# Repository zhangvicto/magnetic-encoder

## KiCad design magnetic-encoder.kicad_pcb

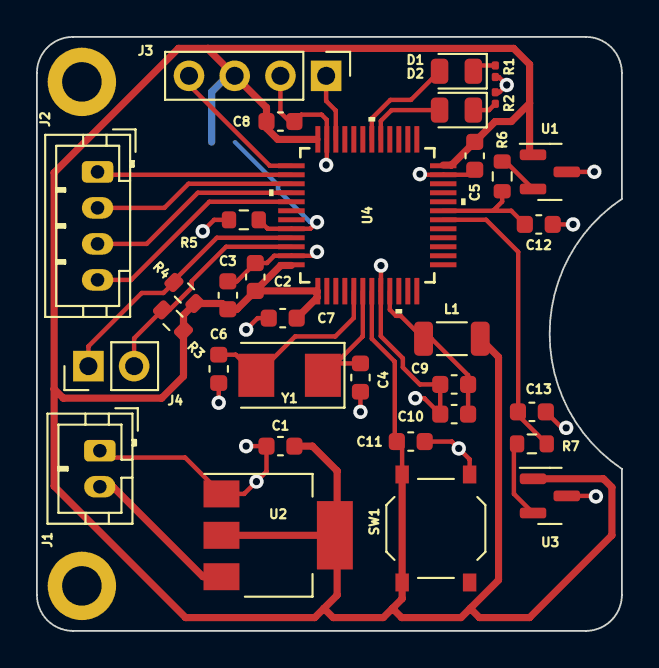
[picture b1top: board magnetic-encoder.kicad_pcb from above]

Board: 2 copper layers, 32.5 x 33.0 mm, 36 parts (1 on the bottom side), 23 nets.

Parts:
C1, C9: 1u; C_0603_1608Metric
C2: 4u7; C_0603_1608Metric
C3, C5, C7, C8, C10, C11: 100n; C_0603_1608Metric
C4, C6: 20p; L_0603_1608Metric
C12, C13: C_Small; C_0603_1608Metric
D1, D2: LED_Small; LED_0805_2012Metric
J1: Conn_01x02_Socket; JST_PH_B2B-PH-K_1x02_P2.00mm_Vertical
J2: Conn_01x04_Socket; JST_PH_B4B-PH-K_1x04_P2.00mm_Vertical
J3: Conn_01x04_Pin; PinHeader_1x04_P2.54mm_Vertical
J4: Conn_01x02_Socket; PinHeader_1x02_P2.54mm_Vertical
JP1: SolderJumper_2_Open; SolderJumper-2_P1.3mm_Open_Pad1.0x1.5mm
L1: 27n; L_1206_3216Metric
R1, R2: 1.5k; R_0201_0603Metric
R3, R4: 4.7k; R_0603_1608Metric
R5: 10k; R_0603_1608Metric
R6, R7: R_Small; R_0603_1608Metric
REF1, REF2: MountingHole_2.2mm_M2_DIN965_Pad
SW1: SW_Push; SW_Push_1P1T_XKB_TS-1187A
U1, U3: DRV5055A4xDBZxQ1; SOT-23
U2: AMS1117-3.3; SOT-223-3_TabPin2
U4: STM32F103C8T6; LQFP48_STM
Y1: 8Mhz; Crystal_SMD_5032-2Pin_5.0x3.2mm

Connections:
+3.3V: C1.1, C2.1, C3.1, C5.1, C7.1, C8.1, C11.1, J3.3, JP1.2 (B), L1.1, R3.1, R4.1, SW1.2, U1.1 (VCC), U2.2 (VO), U3.1 (VCC), U4.1 (VBAT), U4.7 (NRST), U4.24 (VDD_1), U4.36 (VDD_2), U4.48 (VDD_3)
+3.3VA: C9.1, C10.1, L1.2, U4.9 (VDDA)
+5V: J1.2, U2.3 (VI)
BOOT0: JP1.1 (A), R5.1, U4.44 (BOOT0)
GND: C1.2, C2.2, C3.2, C4.2, C5.2, C6.2, C7.2, C8.2, C9.2, C10.2, C11.2, C12.2, C13.2, J1.1, J3.2, R1.1, R2.1, R5.2, SW1.1, U1.3 (GND), U2.1 (GND), U3.3 (GND), U4.8 (VSSA), U4.23 (VSS_1), U4.35 (VSS_2), U4.47 (VSS_3)
HAL1_IN: C12.1, R6.2, U4.19 (PB1-ADC1_IN9)
HAL2_IN: C13.1, R7.2, U4.18 (PB0-ADC1_IN8)
I2C1_SCL: J4.1, R4.2, U4.45 (PB8)
I2C1_SDA: J4.2, R3.2, U4.46 (PB9)
unnamed: D1.2 (A), U4.30 (PA9)
unnamed: D1.1 (K), R1.2
unnamed: D2.2 (A), U4.29 (PA8)
unnamed: D2.1 (K), R2.2
unnamed: R6.1, U1.2 (OUT)
unnamed: R7.1, U3.2 (OUT)
unnamed: C6.1, U4.5 (PD0-OSC_IN-RCC_OSC_IN), Y1.2
unnamed: C4.1, U4.6 (PD1-OSC_OUT-RCC_OSC_OUT), Y1.1
SPI1_MISO: J2.3, U4.40 (PB4-SPI1_MISO)
SPI1_MOSI: J2.4, U4.41 (PB5-SPI1_MOSI)
SPI1_NSS: J2.1, U4.38 (PA15-SPI1_NSS)
SPI1_SCK: J2.2, U4.39 (PB3-SPI1_SCK)
SWCLK: J3.4, U4.37 (PA14-SYS_JTCK-SWCLK)
SWDIO: J3.1, U4.34 (PA13-SYS_JTMS-SWDIO)

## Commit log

2024-09-26 init
